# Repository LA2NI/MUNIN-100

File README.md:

# MUNIN-100
MUNIN 100 is a 100W HF Power Amplifier using the MRF101AN/MRF101BN at 48V DC supply voltage.

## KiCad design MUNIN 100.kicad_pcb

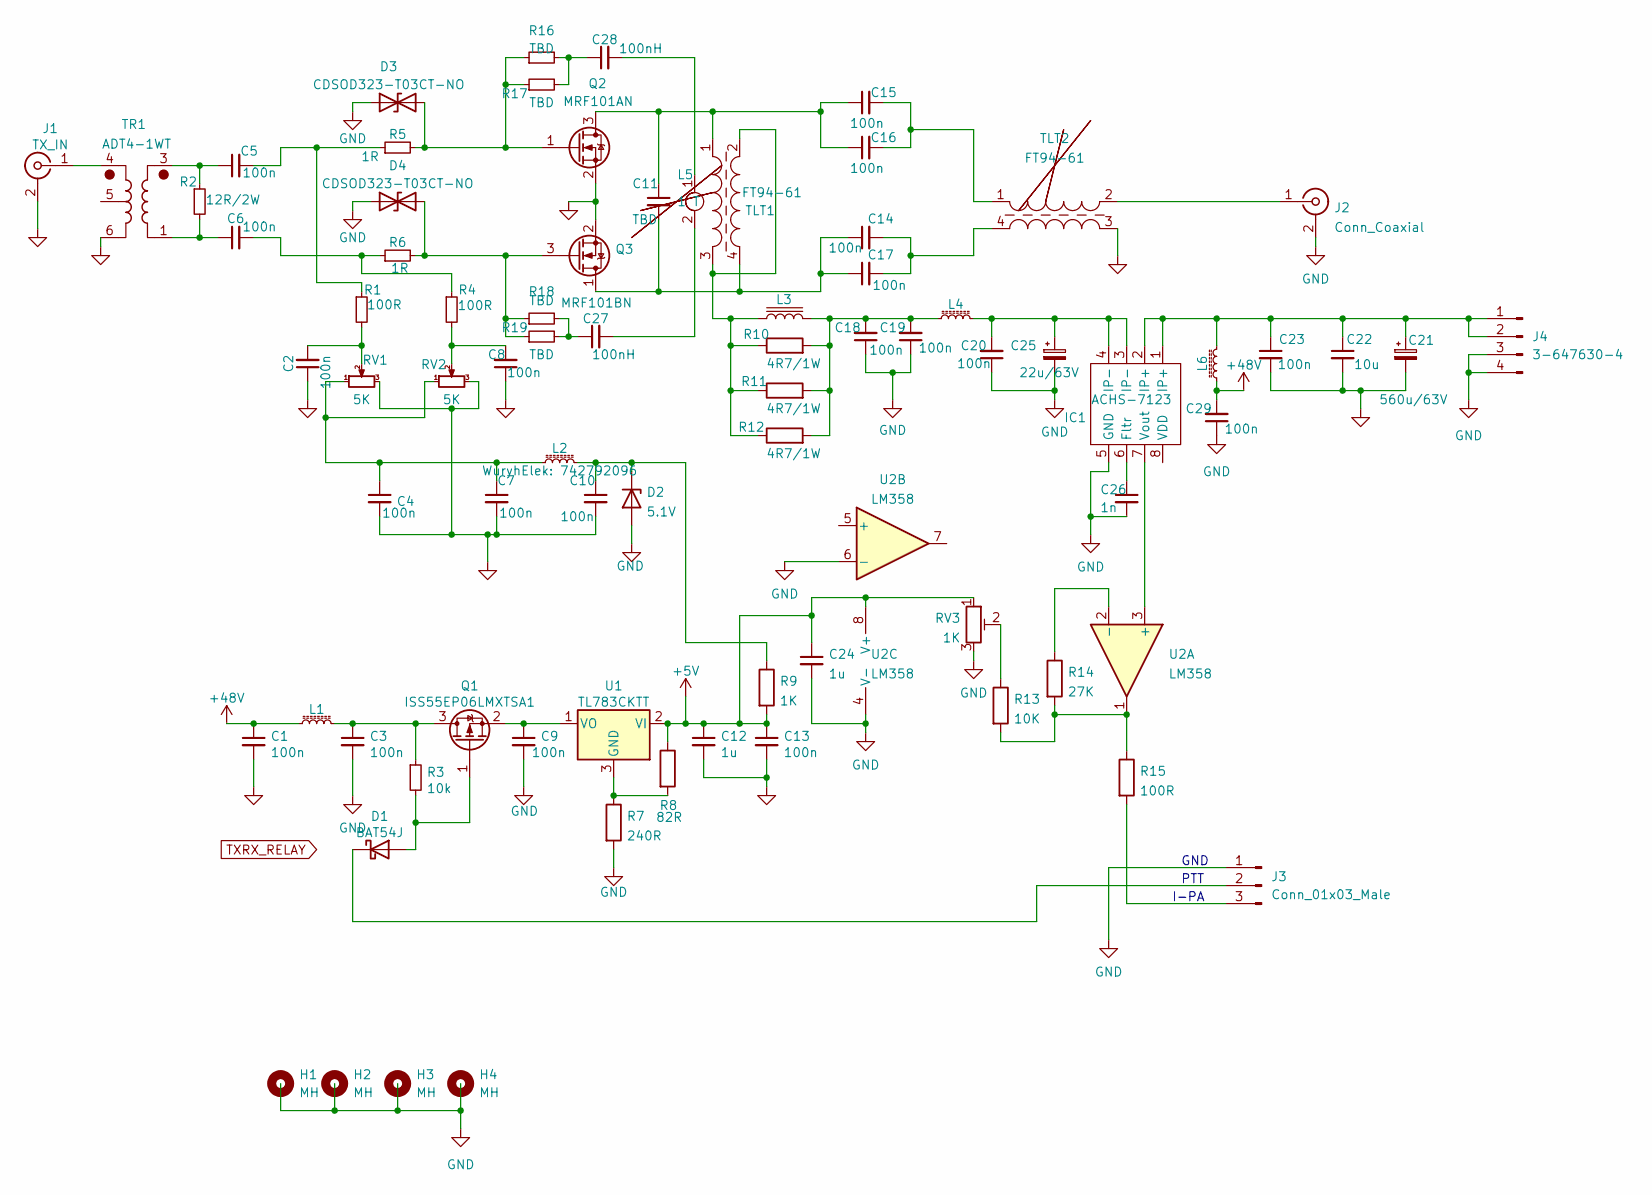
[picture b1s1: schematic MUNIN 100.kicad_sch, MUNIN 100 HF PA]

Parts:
C1: 100n; C_0805_2012Metric
C2, C3, C4, C5, C6, C7, C8, C9, C10, C13, C18, C19, C20, C23, C29: 100n; C_0805_2012Metric_Pad1.18x1.45mm_HandSolder
C11: TBD; C_1210_3225Metric
C12, C24: 1u; C_0805_2012Metric_Pad1.18x1.45mm_HandSolder
C14, C15, C16, C17: 100n; C_1210_3225Metric_Pad1.33x2.70mm_HandSolder
C21: 560u/63V; CP_Elec_16x17.5
C22: 10u; C_0805_2012Metric_Pad1.18x1.45mm_HandSolder
C25: 22u/63V; CP_Elec_10x14.3
C26: 1n; C_0805_2012Metric_Pad1.18x1.45mm_HandSolder
C27, C28: 100nH; C_0805_2012Metric
D1: BAT54J; D_MELF
D2: 5.1V; D_0603_1608Metric
D3, D4: CDSOD323-T03CT-NO; D_0805_2012Metric
H1, H2, H3, H4: MH; MountingHole_3.2mm_M3
IC1: ACHS-7123; SO-8_5.3x6.2mm_P1.27mm
J1: TX_IN; SMA_Amphenol_132291_Vertical
J2: Conn_Coaxial; SMA_Amphenol_132291_Vertical
J3: Conn_01x03_Male; PinHeader_1x03_P2.54mm_Horizontal
J4: 3-647630-4; PinHeader_1x04_P2.54mm_Horizontal
L1: 742792096; L_0805_2012Metric_Pad1.05x1.20mm_HandSolder
L2: WuryhElek: 742792096; L_0805_2012Metric_Pad1.05x1.20mm_HandSolder
L3: FT-50-43; FT_50_1
L4: HI1806T600R-10; L_1812_4532Metric
L5: 1 T; L_1812_4532Metric
L6: L_Core_Ferrite_Small; L_0805_2012Metric_Pad1.05x1.20mm_HandSolder
Q1: ISS55EP06LMXTSA1; SOT-23
Q2: MRF101AN; TO-220-3_Horizontal_TabDown_SMD
Q3: MRF101BN; TO-220-3_Horizontal_TabDown_SMD
R1, R4, R15: 100R; R_0805_2012Metric_Pad1.20x1.40mm_HandSolder
R2: 12R/2W; R_2512_6332Metric
R3: 10k; R_0805_2012Metric_Pad1.20x1.40mm_HandSolder
R5, R6: 1R; R_0805_2012Metric_Pad1.20x1.40mm_HandSolder
R7: 240R; R_0805_2012Metric_Pad1.20x1.40mm_HandSolder
R8: 82R; R_0805_2012Metric_Pad1.20x1.40mm_HandSolder
R9: 1K; R_0805_2012Metric_Pad1.20x1.40mm_HandSolder
R10, R11, R12: 4R7/1W; R_1210_3225Metric
R13: 10K; R_0805_2012Metric_Pad1.20x1.40mm_HandSolder
R14: 27K; R_0805_2012Metric_Pad1.20x1.40mm_HandSolder
R16, R17, R18, R19: TBD; R_1206_3216Metric
RV1, RV2: 5K; Potentiometer_Bourns_3214G_Horizontal
RV3: 1K; Potentiometer_Bourns_3214G_Horizontal
TLT1, TLT2: FT94-61; TLT_94_3
TR1: ADT4-1WT; Mini-Circuits_CD542_H2.84mm
U1: TL783CKTT; TO-263-3_TabPin2
U2: LM358; Diodes_PSOP-8

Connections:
+5V: C12.1, C13.1, C24.1, R8.1, R9.2, RV3.1, U1.2 (VI), U2.8 (V+)
+48V: C1.1, C29.2, L1.1, L6.1
GND: C1.2, C2.1, C3.2, C4.2, C7.2, C8.1, C9.2, C10.2, C12.2, C13.2, C18.1, C19.1, C20.1, C21.2, C22.2, C23.2, C24.2, C25.2, C26.2, C29.1, D2.2 (A), D3.1 (A1), D4.1 (A1), IC1.5 (GND), J1.2 (Ext), J2.2 (Ext), J3.1, J4.3, J4.4, Q2.2 (S), Q3.2 (S), R7.2, RV1.3, RV2.3, RV3.3, TLT2.3, TR1.6, U2.4 (V-), U2.6 (-)
unnamed: C2.2, R1.2, RV1.2
unnamed: C3.1, L1.2, Q1.3 (D), R3.1
unnamed: C4.1, C7.1, L2.1, RV1.1, RV2.1
unnamed: C5.1, R2.1, TR1.3
unnamed: C5.2, R1.1, R5.1
unnamed: C6.1, R2.2, TR1.1
unnamed: C6.2, R4.1, R6.1
unnamed: C8.2, R4.2, RV2.2
unnamed: C9.1, Q1.2 (S), U1.1 (VO)
unnamed: C10.1, D2.1 (K), L2.2, R9.1
unnamed: C11.1, C15.1, C16.1, Q2.3 (D), TLT1.1
unnamed: C11.2, C14.1, C17.1, Q3.1 (D), TLT1.4
unnamed: C14.2, C17.2, TLT2.4
unnamed: C15.2, C16.2, TLT2.1
unnamed: C18.2, C19.2, L3.2, L4.1, R10.2, R11.2, R12.2
unnamed: C20.2, C25.1, IC1.3 (IP-), IC1.4 (IP-), L4.2
unnamed: C21.1, C22.1, C23.1, IC1.1 (IP+), IC1.2 (IP+), J4.1, J4.2, L6.2
unnamed: C26.1, IC1.6 (Fltr)
unnamed: C27.1, R18.2, R19.2
unnamed: C27.2, L5.2
unnamed: C28.1, R16.2, R17.2
unnamed: C28.2, L5.1
unnamed: D1.1 (K), J3.2
unnamed: D1.2 (A), Q1.1 (G), R3.2
unnamed: D3.2 (A2), Q2.1 (G), R5.2, R16.1, R17.1
unnamed: D4.2 (A2), Q3.3 (G), R6.2, R18.1, R19.1
unnamed: IC1.7 (Vout), U2.3 (+)
unnamed: J1.1 (In), TR1.4
unnamed: J2.1 (In), TLT2.2
unnamed: J3.3, R15.2
unnamed: L3.1, R10.1, R11.1, R12.1, TLT1.2, TLT1.3
unnamed: R7.1, R8.2, U1.3 (GND)
unnamed: R13.1, RV3.2
unnamed: R13.2, R14.2, R15.1, U2.1
unnamed: R14.1, U2.2 (-)

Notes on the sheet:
GND
PTT
I-PA

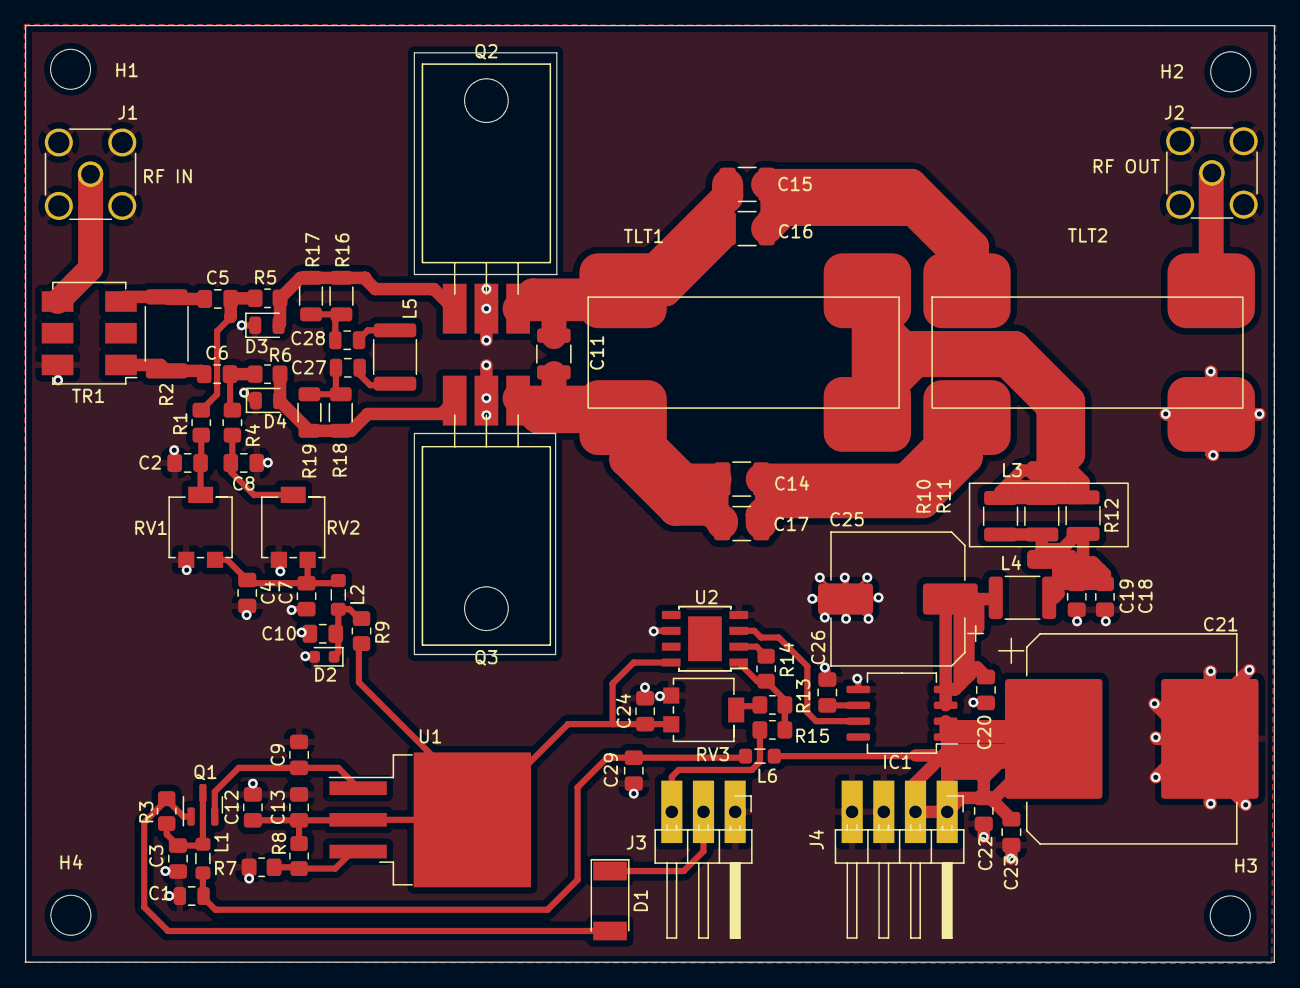
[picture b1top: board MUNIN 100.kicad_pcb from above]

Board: 2 copper layers, 100.0 x 75.0 mm, 78 parts (0 on the bottom side), 38 nets.

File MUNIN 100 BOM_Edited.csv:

Id;Designator;Package;Quantity;Designation;Part number;Alternative PN;
1;C1;C_0805_2012Metric;1;100nF;;;
2;Q3;TO-220-3_Horizontal_TabDown_SMD;1;MRF101BN;MRF101BN;;
3;R1,R4,R15;R_0805_2012Metric_Pad1.20x1.40mm_HandSolder;3;100R;;;
4;U2;Diodes_PSOP-8;1;LM358;;;
5;C8,C7,C19,C23,C9,C5,C3,C2,C20,C10,C29,C13,C6,C18,C4;C_0805_2012Metric_Pad1.18x1.45mm_HandSolder;15;100nF;;;
6;L1,L2,L6;L_0805_2012Metric_Pad1.05x1.20mm_HandSolder;3;L_Core_Ferrite_Small;BLM21SP102SN1D;;
7;C12,C24;C_0805_2012Metric_Pad1.18x1.45mm_HandSolder;2;1u;;;.
8;L4;L_1812_4532Metric;1;Ferrite;FBMH4532HM681-T;HI1806T600R-10;
9;C14,C15,C17,C16;C_1210_3225Metric_Pad1.33x2.70mm_HandSolder;4;100n/500V;;;
10;C26;C_0805_2012Metric_Pad1.18x1.45mm_HandSolder;1;1n;;;
11;R7;R_0805_2012Metric_Pad1.20x1.40mm_HandSolder;1;240R;;;
12;IC1;SO-8_5.3x6.2mm_P1.27mm;1;ACHS-7123;;;
13;R18,R16,R17,R19;R_1206_3216Metric;4;TBD;;;
14;C25;CP_Elec_10x14.3;1;220uF/63V;EEV-FK1J221Q;Panasonic;
15;TR1;Mini-Circuits_CD542_H2.84mm;1;ADT4-1WT;ADT4-1WT+;Mini Circuits;
16;D1;D_MELF;1;BAT54J;;;
17;C11;C_1210_3225Metric;1;TBD;;;
19;D3,D4;D_0805_2012Metric;2;CDSOD323-T03CT-NO;;;
20;C21;CP_Elec_16x17.5;1;560u/63V;EEE-TP1J561V;Panasonic;
21;R10,R12,R11;R_1210_3225Metric;3;4R7/1W;;;
22;L5;L_1812_4532Metric;1;;;;
23;C27,C28;C_0805_2012Metric;2;100nH;;1;
24;J3;PinHeader_1x03_P2.54mm_Horizontal;1;Conn_01x03_Male;;;
25;RV3;Potentiometer_Bourns_3214G_Horizontal;1;1K;3214G-1-102E ;;
26;RV1,RV2;Potentiometer_Bourns_3214G_Horizontal;2;5K;3214G-1-502E ;;
27;J1,J2;SMA_Amphenol_132291_Vertical;1;SMA;142-0701-201;CONSMA002-L-G;
28;Q2;TO-220-3_Horizontal_TabDown_SMD;1;MRF101AN;MRF101AN;;
29;D2;D_0603_1608Metric;1;5.1V;;;
30;J4;PinHeader_1x04_P2.54mm_Horizontal;1;3-647630-4;;;
31;TLT2,TLT1;TLT_94_3;2;FT94-61 or FT82-61;Kitsandparts.com;Reichelt Elektron.;
32;U1;TO-263-3_TabPin2;1;TL783CKTT;TL783CKTT;;
33;R6,R5;R_0805_2012Metric_Pad1.20x1.40mm_HandSolder;2;1R;;;
34;Q1;SOT-23;1;ISS55EP06LMXTSA1;ISS55EP06LMXTSA1;;
35;R14;R_0805_2012Metric_Pad1.20x1.40mm_HandSolder;1;27K;;;
36;R9;R_0805_2012Metric_Pad1.20x1.40mm_HandSolder;1;1K;;;
37;C22;C_0805_2012Metric_Pad1.18x1.45mm_HandSolder;1;10u;;;
38;R3;R_0805_2012Metric_Pad1.20x1.40mm_HandSolder;1;10k;;;
39;R13;R_0805_2012Metric_Pad1.20x1.40mm_HandSolder;1;10K;CRM2512-FX-12R0ELF;;
40;R2;R_2512_6332Metric;1;12R/2W;;;
41;R8;R_0805_2012Metric_Pad1.20x1.40mm_HandSolder;1;82R;;;
42;L3;FT_50_1;1;FT50-43;Kitsandparts.com;;
;;;;;;;
;;;1;;;;

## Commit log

2022-01-25 Replaced SMA Conectors
2022-01-25 Updated SMA Connectors 3-d
2022-01-26 Added Gerber files
2022-01-28 Updated BOM
2022-01-28 Create .~lock.MUNIN 100_Edited.csv#
